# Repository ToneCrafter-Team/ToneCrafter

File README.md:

<h1 align=left>&emsp;ToneCrafter</h1>

ToneCrafter is a project developped by students at [ENSEA](https://www.ensea.fr/).  
Our goal is to develop an algorithm capable of analyzing any audio file containing guitar sounds and retrieve its parameters. ToneCrafter will then generate a numeric filter that will modulate your guitar sound and make it sound like the recording you fed it. Exciting isn't it ?  
We are also working on a hardware implementation using a STM32 µC that will allow musicians to use ToneCrafter on stage and tune the different parameters.

- [Our work so far](#our-work-so-far)
  * [Software](#Software)
  * [Hardware](#Hardware)
- [How to use ToneCrafter](#how-to-use-tonecrafter)
  * [Installing Anaconda and TensorFlow](#installing-anaconda-and-tensorflow)
  * [Dataset](#dataset)
  * [Useful links](#useful-links)
- [What's next ?](#whats-next-)

## Our work so far
### Software
We started out trying to use Magenta's [DDSP](https://www.github.com/magenta/ddsp), but this was a bit too ambitious for AI newbies like us, so we tried implementing our own algorithms.  
This sparked three different approaches to our problem:  
  * A CNN based approach where we tried to teach a neural network to recreate a distortion.
  * A "bare coding" approach using math and clever algorithms to recreate a distortion from an audio file
  * A VAE based approach trying to recreate the mechanisms behind Magenta's DDSP

### Hardware
We started working on different PCB designs using [Eagle](https://www.autodesk.com/products/eagle/overview) and working on a STM32F7 discovery kit for testing purposes.

## How to use ToneCrafter
### Installing Anaconda and TensorFlow
To begin with, if you want to work locally and not on Colabs as we did, you will have to install Anaconda.
To do this follow the [officials instructions](https://docs.anaconda.com/anaconda/user-guide/tasks/tensorflow/) that are given to you.  

If you want to try the huge potential of DDSP, let’s check the [DDSP GitHub](https://github.com/magenta/ddsp) which show how to install it.
There are also some tutorials to introduce the main concepts of the library (that we strongly recommend you to do) and demos to show what you can do with it (Like Timbre transfer, Train Autoencoder and Pitch Detection).

And then, if you want to have fun on the models created by the Google team with the [Magenta](https://magenta.tensorflow.org/) project, follow the installation guide on their [page](https://github.com/magenta/magenta).

### Dataset
To train our CNN, we searched for a dataset containing clean audio from a guitar and different distortions. As we could not find any we had to create our own. We recorded a guitar for 1 minute and added various levels of distortion. To increase the size of our base, we applied an EQ filter with various settings.  
We ended up with a lot of .wav files that you can find [here](https://github.com/ToneCrafter-Team/ToneCrafter/tree/main/Software/CNN%20Models/Dataset).  
In order to train our CNN, we splitted our files in 200ms chunks using our [Preparing Data Notebook](https://github.com/ToneCrafter-Team/ToneCrafter/blob/main/Software/CNN%20Models/Preparing_Data.ipynb)  
We then organised our files in the following way :  

- X_train :  
  * Clean  
  * Clean_TrebbleBoost  
  * Clean_BassBoost  
  * Clean_BassCut  

- y_train :
  * Disto  
  * Disto_TrebbleBoost  
  * Disto_BassBoost  
  * Disto_BassCut  

- Validation data :
  * Clean_TrebbleCut as X_valid  
  * Disto_TrebbleCut as y_valid  

We are concious that this dataset is far from perfect (please don't listen to it, the guitar playing is awful) from a recording standpoint and the way we splitted our audio might cause some problems.

For the maths oriented approach, we used the excellent [IDMT-SMT-Audio_Effects Dataset](https://www.idmt.fraunhofer.de/en/business_units/m2d/smt/audio_effects.html), which enabled us to link each note played to it's distorted counterpart.  

<span style="color:red"> *For a more in-depths version of this readme, checkout our (magnificent) project report available in both French and English at the root of this repository*</span>
## What's next ?
As of the 03/05/2021, our yearly project has ended. We will continue to work on ToneCrafter at a lighter pace, as we'll be completing our summer internships. If all goes well, some new students will pick up the project in the fall to continue to build on top of our work. In the mean time, don't hesitate to take part in our project, via issues or pull requests.

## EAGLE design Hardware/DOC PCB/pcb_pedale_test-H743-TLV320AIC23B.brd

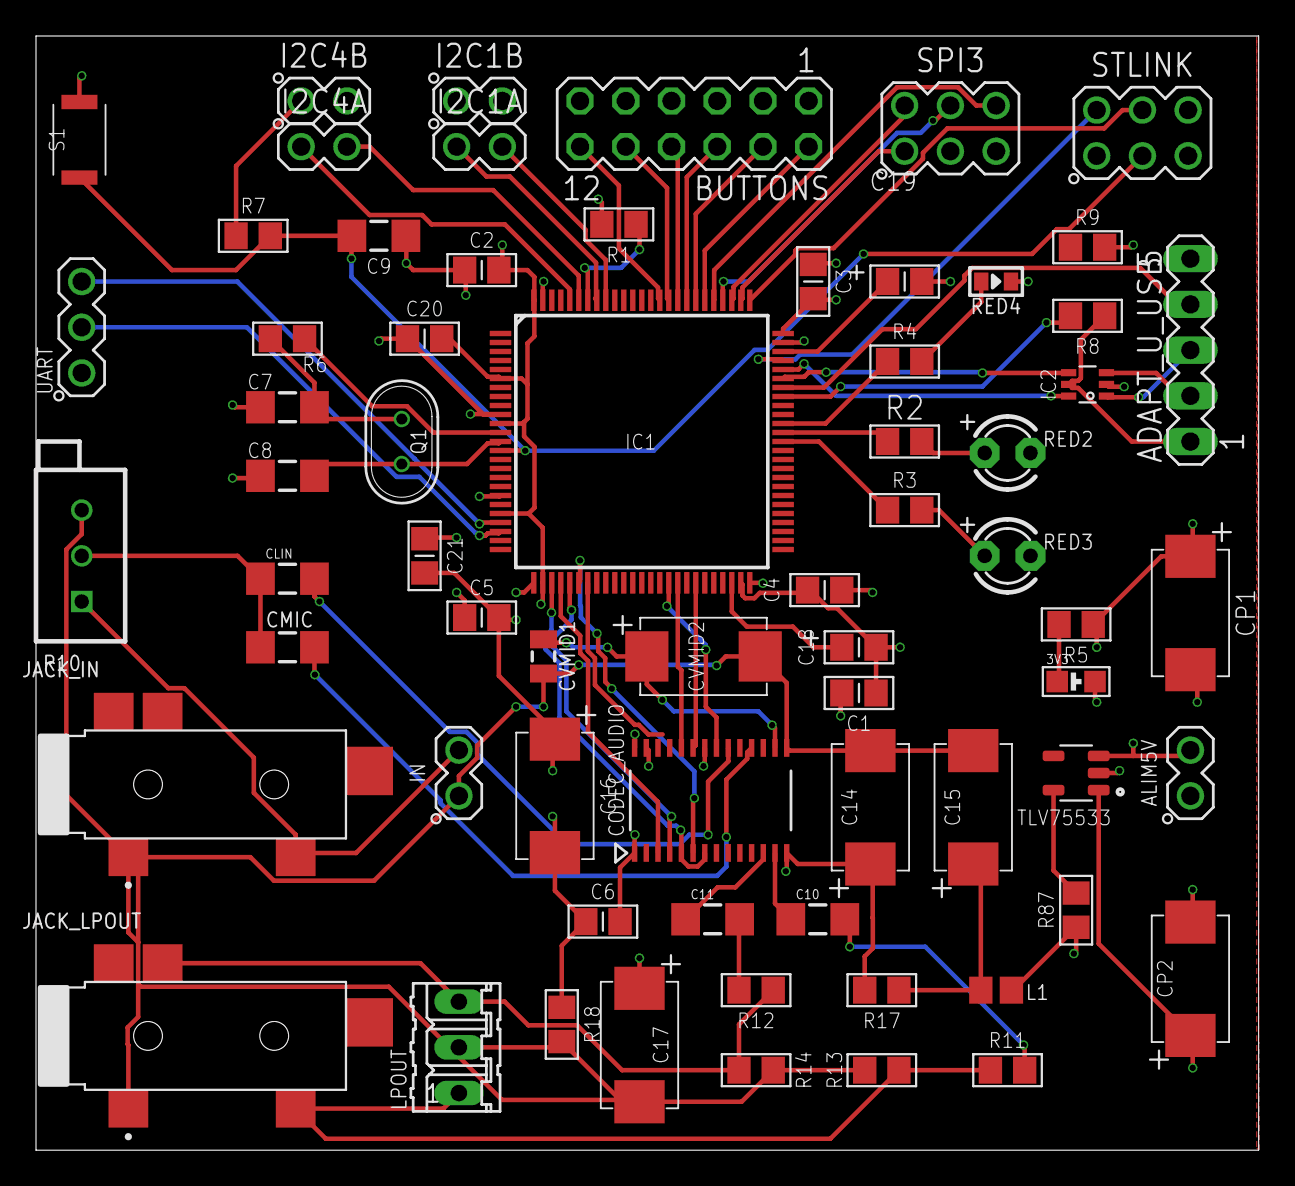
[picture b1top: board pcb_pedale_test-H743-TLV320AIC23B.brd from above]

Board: 4 copper layers, 67.9 x 61.9 mm, 67 parts (0 on the bottom side), 65 nets.

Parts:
3V3: 0805-LED
ADAPT_U_USB: MA05-1
ALIM5V: MA02-1
BUTTONS: MA06-2
C1, C2, C3, C4, C5, C20, C21: 0.1uF; C0805
C6: 0.1u; C0805
C7, C8: 12pF; 1206
C9: 0.1uF; 1206
C10, C11: 1u; 1206
C14, C15, C16, C17: 10u; CPOL2917
C18, C19: 2.2u; CPOL0805
CLIN: 1u; 1206
CMIC: 1u; 1206
CODEC_AUDIO: TLV320AIC23B; TSSOP28
CP1: 100 uF; CPOL2917
CP2: 10u; CPOL2917
CVMID1: 100n; 0805-CAP
CVMID2: 10u; CPOL2917
I2C1A, I2C1B, I2C4A, I2C4B: MA02-1
IC1: STM32H743VIT1Q; LQFP100_14X14
IC2: SC70-6
IN: MA02-1
JACK_IN: 35RASMT4BHNTRX
JACK_LPOUT: 35RASMT4BHNTRX
L1: FB805
LPOUT: 03P
Q1: 16MHz; Q-HC-46X
R1: 10K; R0805
R2, R3, R4: 180; R0805
R5: 1k; R0805
R6, R11, R12: 100; R0805
R7, R13, R14: 100k; R0805
R8: 4.7k; R0805
R9: 10k; R0805
R10: POT-PTH
R17: 2.2; R0805
R18, R87: 0; R0805
RED2, RED3: LED3MM
RED4: 0603-LED
S1: SWITCH-SKRKAEE020; SKRKAEE020
SPI3: MA03-2
STLINK: 75867-331LF; MA03-2
TLV75533: TLV75533PDBVR; SOT95P280X145-5N
UART: MA03-1

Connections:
3V3: C1.2, C2.2, C3.2, C4.2, C5.2, C6.2, C16.+, C20.2, C21.2, CODEC_AUDIO.1, CODEC_AUDIO.22, CODEC_AUDIO.27, CP1.+, I2C1B.2, I2C4B.1, IC1.6, IC1.11, IC1.21, IC1.27, IC1.50, IC1.75, IC1.100, L1.1, R5.1, R7.1, R87.1, SPI3.5, STLINK.1
3V3A: C14.+, C17.+, CODEC_AUDIO.14, R17.2
5V: ALIM5V.2, CP2.+, TLV75533.1, TLV75533.3
AGND: C14.-, C15.-, C17.-, CODEC_AUDIO.15, CVMID1.2, CVMID2.-, IN.1, JACK_IN.1, JACK_LPOUT.1, LPOUT.2, R10.3, R13.2, R14.2, R18.2
DM: ADAPT_U_USB.2, IC2.3
DP: ADAPT_U_USB.3, IC2.1
GND: 3V3.C, ADAPT_U_USB.5, ALIM5V.1, BUTTONS.1, BUTTONS.3, BUTTONS.5, BUTTONS.7, BUTTONS.9, BUTTONS.11, C1.1, C2.1, C3.1, C4.1, C5.1, C6.1, C7.1, C8.1, C9.1, C16.-, C18.2-, C19.2-, C20.1, C21.1, CODEC_AUDIO.28, CP1.-, CP2.-, I2C1B.1, I2C4B.2, IC1.10, IC1.19, IC1.26, IC1.49, IC1.74, IC1.99, IC2.2, R1.2, R9.2, R18.1, RED2.K, RED3.K, RED4.C, S1.1, SPI3.3, STLINK.5, TLV75533.2, UART.1
HOME: BUTTONS.12, IC1.86
I2S_CK: CODEC_AUDIO.3, IC1.29
I2S_DI: CODEC_AUDIO.4, IC1.30
I2S_DO: CODEC_AUDIO.6, IC1.31
I2S_MCK: CODEC_AUDIO.25, IC1.32
I2S_WS: CODEC_AUDIO.5, CODEC_AUDIO.7, IC1.28
JACK_OUT_L: JACK_LPOUT.2, LPOUT.3, R12.1, R14.1
JACK_OUT_R: JACK_LPOUT.3, LPOUT.1, R11.1, R13.1
LED2_PWM: IC1.64, R2.1
LED3_PWM: IC1.63, R3.1
LED4_PWM: IC1.65, R4.1
LOUT: C11.1, CODEC_AUDIO.12
MICIN: CMIC.2, CODEC_AUDIO.18
unnamed: IC1.94, R1.1
unnamed: C11.2, R12.2
unnamed: R2.2, RED2.A
unnamed: IC1.12, R6.1
unnamed: R3.2, RED3.A
unnamed: C10.2, R11.2
unnamed: CLIN.2, CODEC_AUDIO.20
unnamed: C15.+, L1.2, R17.1
unnamed: C18.1+, IC1.48
unnamed: C19.1+, IC1.73
unnamed: CLIN.1, CMIC.1, R10.2
unnamed: IN.2, JACK_IN.3, R10.1
unnamed: R4.2, RED4.A
unnamed: CODEC_AUDIO.16, CVMID1.1, CVMID2.+
unnamed: 3V3.A, R5.2
unnamed: C7.2, Q1.1, R6.2
unnamed: R87.2, TLV75533.5
NRST: C9.2, IC1.14, R7.2, S1.2, STLINK.3
OSC_OUT: C8.2, IC1.13, Q1.2
PRESSION: BUTTONS.6, IC1.83
ROTATE_X: BUTTONS.4, IC1.82
ROTATE_Y: BUTTONS.2, IC1.81
ROUT: C10.1, CODEC_AUDIO.13
RX: IC1.23, UART.2
SCL_1: I2C4A.2, IC1.95
SCL_4: I2C1A.2, IC1.92
SDA_1: I2C4A.1, IC1.96
SDA_4: I2C1A.1, IC1.93
SPI3_MISO: IC1.79, SPI3.4
SPI3_MOSI: IC1.80, SPI3.6
SPI3_NSS: IC1.77, SPI3.1
SPI3_SCK: IC1.78, SPI3.2
SPI4_MOSI: CODEC_AUDIO.23, IC1.44
SPI4_NSS: CODEC_AUDIO.21, IC1.41
SPI4_SCK: CODEC_AUDIO.24, IC1.42
STOMP1: BUTTONS.8, IC1.84
STOMP2: BUTTONS.10, IC1.85
SWCLK: IC1.76, STLINK.4
SWDIO: IC1.72, STLINK.2
TX: IC1.22, UART.3
USB_ID: ADAPT_U_USB.4, IC1.69
USB_OTG_FS_DM: IC1.70, IC2.4
USB_OTG_FS_DP: IC1.71, IC2.6
USB_OTG_FS_VBUS: ADAPT_U_USB.1, IC2.5, R8.1
USB_OTG_FS_VBUS_3V3: IC1.68, R8.2, R9.1

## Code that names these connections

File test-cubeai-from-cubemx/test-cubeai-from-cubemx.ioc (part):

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Mcu.Name=STM32F746NGHx
Mcu.Package=TFBGA216
Mcu.UserName=STM32F746NGHx
PA0/WKUP.GPIOParameters=GPIO_PuPd,GPIO_Label,GPIO_Mode
PA0/WKUP.GPIO_Label=ARDUINO A0
PA0/WKUP.GPIO_Mode=GPIO_MODE_ANALOG
PA0/WKUP.GPIO_PuPd=GPIO_NOPULL
PA0/WKUP.Signal=ADCx_IN0
PA1.GPIOParameters=GPIO_Label
PA1.GPIO_Label=RMII_REF_CLK [LAN8742A-CZ-TR_REFCLK0]
PA1.Mode=RMII
PA1.Signal=ETH_REF_CLK
PA10.GPIOParameters=GPIO_Label
PA10.GPIO_Label=OTG_FS_ID
PA10.Signal=USB_OTG_FS_ID
PA11.GPIOParameters=GPIO_Label
PA11.GPIO_Label=OTG_FS_N
PA11.Mode=Host_Only
PA11.Signal=USB_OTG_FS_DM
PA12.GPIOParameters=GPIO_Label
PA12.GPIO_Label=OTG_FS_P
PA12.Mode=Host_Only
PA12.Signal=USB_OTG_FS_DP
PA13.GPIOParameters=GPIO_Label
PA13.GPIO_Label=SWDIO
PA13.Mode=Serial_Wire
PA13.Signal=SYS_JTMS-SWDIO
PA14.GPIOParameters=GPIO_Label
PA14.GPIO_Label=SWCLK
PA14.Mode=Serial_Wire
PA14.Signal=SYS_JTCK-SWCLK
PA15.GPIOParameters=GPIO_ModeDefaultPP,GPIO_Speed,GPIO_PuPd,GPIO_Label
PA15.GPIO_Label=ARDUINO PWM/D9
PA15.GPIO_ModeDefaultPP=GPIO_MODE_AF_PP
PA15.GPIO_PuPd=GPIO_NOPULL
PA15.GPIO_Speed=GPIO_SPEED_FREQ_LOW
PA15.Signal=S_TIM2_CH1_ETR
PA2.GPIOParameters=GPIO_Label
PA2.GPIO_Label=RMII_MDIO [LAN8742A-CZ-TR_MDIO]
PA2.Mode=RMII
PA2.Signal=ETH_MDIO
PA3.GPIOParameters=GPIO_Label
PA3.GPIO_Label=ULPI_D0 [USB3320C-EZK_D0]
PA3.Mode=Host_HS
PA3.Signal=USB_OTG_HS_ULPI_D0
PA4.GPIOParameters=GPIO_Label
PA4.GPIO_Label=DCMI_HSYNC
PA4.Mode=Slave_8_bits_External_Synchro
PA4.Signal=DCMI_HSYNC
PA5.GPIOParameters=GPIO_Label
PA5.GPIO_Label=ULPI_CLK [USB3320C-EZK_CLKOUT]
PA5.Mode=Host_HS
PA5.Signal=USB_OTG_HS_ULPI_CK
PA6.Mode=Slave_8_bits_External_Synchro
PA6.Signal=DCMI_PIXCLK
PA7.GPIOParameters=GPIO_Label
PA7.GPIO_Label=RMII_CRS_DV [LAN8742A-CZ-TR_CRS_DV]
PA7.Mode=RMII
PA7.Signal=ETH_CRS_DV
PA8.GPIOParameters=GPIO_ModeDefaultPP,GPIO_Speed,GPIO_PuPd,GPIO_Label
PA8.GPIO_Label=ARDUINO PWM/D10
PA8.GPIO_ModeDefaultPP=GPIO_MODE_AF_PP
PA8.GPIO_PuPd=GPIO_NOPULL
PA8.GPIO_Speed=GPIO_SPEED_FREQ_LOW
PA8.Signal=S_TIM1_CH1
PA9.GPIOParameters=GPIO_Speed,GPIO_PuPd,GPIO_Label,GPIO_Mode
PA9.GPIO_Label=VCP_TX [STM32F103CBT6_PA3]
PA9.GPIO_Mode=GPIO_MODE_AF_PP
PA9.GPIO_PuPd=GPIO_NOPULL
PA9.GPIO_Speed=GPIO_SPEED_FREQ_LOW
PA9.Mode=Asynchronous
PA9.Signal=USART1_TX
PB0.GPIOParameters=GPIO_Label
PB0.GPIO_Label=ULPI_D1 [USB3320C-EZK_D1]
PB0.Mode=Host_HS
PB0.Signal=USB_OTG_HS_ULPI_D1
PB1.GPIOParameters=GPIO_Label
PB1.GPIO_Label=ULPI_D2 [USB3320C-EZK_D2]
PB1.Mode=Host_HS
PB1.Signal=USB_OTG_HS_ULPI_D2
PB10.GPIOParameters=GPIO_Label
PB10.GPIO_Label=ULPI_D3 [USB3320C-EZK_D3]
PB10.Signal=USB_OTG_HS_ULPI_D3
PB11.GPIOParameters=GPIO_Label
PB11.GPIO_Label=ULPI_D4 [USB3320C-EZK_D4]
PB11.Mode=Host_HS
PB11.Signal=USB_OTG_HS_ULPI_D4
PB12.GPIOParameters=GPIO_Label
PB12.GPIO_Label=ULPI_D5 [USB3320C-EZK_D5]
PB12.Mode=Host_HS
PB12.Signal=USB_OTG_HS_ULPI_D5
PB13.GPIOParameters=GPIO_Label
PB13.GPIO_Label=ULPI_D6 [USB3320C-EZK_D6]
PB13.Mode=Host_HS
PB13.Signal=USB_OTG_HS_ULPI_D6
PB14.GPIOParameters=GPIO_Speed,GPIO_PuPd,GPIO_Label,GPIO_Mode
PB14.GPIO_Label=ARDUINO MISO/D12
PB14.GPIO_Mode=GPIO_MODE_AF_PP
PB14.GPIO_PuPd=GPIO_NOPULL
PB14.GPIO_Speed=GPIO_SPEED_FREQ_LOW
PB14.Signal=SPI2_MISO
PB15.GPIOParameters=GPIO_Speed,GPIO_PuPd,GPIO_Label,GPIO_Mode
PB15.GPIO_Label=ARDUINO MOSI/PWM/D11
PB15.GPIO_Mode=GPIO_MODE_AF_PP
PB15.GPIO_PuPd=GPIO_NOPULL
PB15.GPIO_Speed=GPIO_SPEED_FREQ_LOW
PB15.Signal=SPI2_MOSI
PB2.Mode=Single Bank 1
PB2.Signal=QUADSPI_CLK
PB3.GPIOParameters=GPIO_Label
PB3.GPIO_Label=SWO
PB3.Signal=SYS_JTDO-SWO
PB4.GPIOParameters=GPIO_ModeDefaultPP,GPIO_Speed,GPIO_PuPd,GPIO_Label
PB4.GPIO_Label=ARDUINO PWM/D3
PB4.GPIO_ModeDefaultPP=GPIO_MODE_AF_PP
PB4.GPIO_PuPd=GPIO_NOPULL
PB4.GPIO_Speed=GPIO_SPEED_FREQ_LOW
PB4.Signal=S_TIM3_CH1
PB5.GPIOParameters=GPIO_Label
PB5.GPIO_Label=ULPI_D7 [USB3320C-EZK_D7]
PB5.Mode=Host_HS
PB5.Signal=USB_OTG_HS_ULPI_D7
PB6.GPIOParameters=GPIO_Label
PB6.GPIO_Label=QSPI_NCS [N25Q128A13EF840E_S]
PB6.Mode=Single Bank 1
PB6.Signal=QUADSPI_BK1_NCS
PB7.GPIOParameters=GPIO_Speed,GPIO_PuPd,GPIO_Label,GPIO_Mode
PB7.GPIO_Label=VCP_RX [STM32F103CBT6_PA2]
PB7.GPIO_Mode=GPIO_MODE_AF_PP
PB7.GPIO_PuPd=GPIO_NOPULL
PB7.GPIO_Speed=GPIO_SPEED_FREQ_LOW
PB7.Mode=Asynchronous
PB7.Signal=USART1_RX
PB8.GPIOParameters=GPIO_Speed,GPIO_PuPd,GPIO_Label,GPIO_Pu,GPIO_Mode
PB8.GPIO_Label=ARDUINO SCL/D15
PB8.GPIO_Mode=GPIO_MODE_AF_OD
PB8.GPIO_Pu=GPIO_PULLUP
PB8.GPIO_PuPd=GPIO_NOPULL
PB8.GPIO_Speed=GPIO_SPEED_FREQ_LOW
PB8.Mode=I2C
PB8.Signal=I2C1_SCL
PB9.GPIOParameters=GPIO_Speed,GPIO_PuPd,GPIO_Label,GPIO_Pu,GPIO_Mode
PB9.GPIO_Label=ARDUINO SDA/D14
PB9.GPIO_Mode=GPIO_MODE_AF_OD
PB9.GPIO_Pu=GPIO_PULLUP
PB9.GPIO_PuPd=GPIO_NOPULL
PB9.GPIO_Speed=GPIO_SPEED_FREQ_LOW
PB9.Mode=I2C
PB9.Signal=I2C1_SDA
PC0.GPIOParameters=GPIO_Label
PC0.GPIO_Label=ULPI_STP [USB3320C-EZK_STP]
PC0.Mode=Host_HS
PC0.Signal=USB_OTG_HS_ULPI_STP
PC1.GPIOParameters=GPIO_Label
PC1.GPIO_Label=RMII_MDC [LAN8742A-CZ-TR_MDC]
PC1.Mode=RMII
PC1.Signal=ETH_MDC
PC10.GPIOParameters=GPIO_Label
PC10.GPIO_Label=SDMMC_D2
PC10.Mode=SD_4_bits_Wide_bus
PC10.Signal=SDMMC1_D2
PC11.GPIOParameters=GPIO_Label
PC11.GPIO_Label=SDMMC_D3
PC11.Mode=SD_4_bits_Wide_bus
PC11.Signal=SDMMC1_D3
PC12.GPIOParameters=GPIO_Label
PC12.GPIO_Label=SDMMC_CK
PC12.Mode=SD_4_bits_Wide_bus
PC12.Signal=SDMMC1_CK
PC13.GPIOParameters=GPIO_Label
PC13.GPIO_Label=uSD_Detect
PC13.Signal=GPIO_Input
PC14/OSC32_IN.GPIOParameters=GPIO_Label
PC14/OSC32_IN.GPIO_Label=RCC_OSC32_IN
PC14/OSC32_IN.Mode=LSE-External-Oscillator
PC14/OSC32_IN.Signal=RCC_OSC32_IN
PC15/OSC32_OUT.GPIOParameters=GPIO_Label
PC15/OSC32_OUT.GPIO_Label=RCC_OSC32_OUT
PC15/OSC32_OUT.Mode=LSE-External-Oscillator
PC15/OSC32_OUT.Signal=RCC_OSC32_OUT
PC2.GPIOParameters=GPIO_Label
PC2.GPIO_Label=ULPI_DIR [USB3320C-EZK_DIR]
PC2.Mode=Host_HS
PC2.Signal=USB_OTG_HS_ULPI_DIR
PC3.GPIOParameters=GPIO_Label
PC3.GPIO_Label=FMC_SDCKE0 [MT48LC4M32B2B5-6A_CKE]
PC3.Mode=SdramChipSelect1_1
PC3.Signal=FMC_SDCKE0
PC4.GPIOParameters=GPIO_Label
PC4.GPIO_Label=RMII_RXD0 [LAN8742A-CZ-TR_RXD0]
PC4.Mode=RMII
PC4.Signal=ETH_RXD0
PC5.GPIOParameters=GPIO_Label
PC5.GPIO_Label=RMII_RXD1 [LAN8742A-CZ-TR_RXD1]
PC5.Mode=RMII
PC5.Signal=ETH_RXD1
PC6.GPIOParameters=GPIO_Label
PC6.GPIO_Label=ARDUINO TX/D1
PC6.Mode=Asynchronous
PC6.Signal=USART6_TX
PC7.GPIOParameters=GPIO_Label
PC7.GPIO_Label=ARDUINO RX/D0
PC7.Mode=Asynchronous
PC7.Signal=USART6_RX
PC8.Mode=SD_4_bits_Wide_bus
PC8.Signal=SDMMC1_D0
PC9.Mode=SD_4_bits_Wide_bus
PC9.Signal=SDMMC1_D1
PD0.GPIOParameters=GPIO_Label
PD0.GPIO_Label=FMC_D2 [MT48LC4M32B2B5-6A_DQ2]
PD0.Signal=FMC_D2_DA2
PD1.GPIOParameters=GPIO_Label
PD1.GPIO_Label=FMC_D3 [MT48LC4M32B2B5-6A_DQ3]
PD1.Signal=FMC_D3_DA3
PD10.GPIOParameters=GPIO_Label
PD10.GPIO_Label=FMC_D15 [MT48LC4M32B2B5-6A_DQ15]
PD10.Signal=FMC_D15_DA15
PD11.GPIOParameters=GPIO_Label
PD11.GPIO_Label=QSPI_D0 [N25Q128A13EF840E_DQ0]
PD11.Mode=Single Bank 1
PD11.Signal=QUADSPI_BK1_IO0
PD12.GPIOParameters=GPIO_Label
PD12.GPIO_Label=QSPI_D1 [N25Q128A13EF840E_DQ1]
PD12.Mode=Single Bank 1
PD12.Signal=QUADSPI_BK1_IO1
PD13.GPIOParameters=GPIO_Label
PD13.GPIO_Label=QSPI_D3 [N25Q128A13EF840E_DQ3]
PD13.Mode=Single Bank 1
PD13.Signal=QUADSPI_BK1_IO3
PD14.GPIOParameters=GPIO_Label
PD14.GPIO_Label=FMC_D0 [MT48LC4M32B2B5-6A_DQ0]
PD14.Signal=FMC_D0_DA0
PD15.GPIOParameters=GPIO_Label
PD15.GPIO_Label=FMC_D1 [MT48LC4M32B2B5-6A_DQ1]
PD15.Signal=FMC_D1_DA1
PD2.GPIOParameters=GPIO_Label
PD2.GPIO_Label=SDMMC_CMD
PD2.Mode=SD_4_bits_Wide_bus
PD2.Signal=SDMMC1_CMD
PD3.GPIOParameters=GPIO_Label
PD3.GPIO_Label=DCMI_D5
PD3.Mode=Slave_8_bits_External_Synchro
PD3.Signal=DCMI_D5
PD4.GPIOParameters=GPIO_Label
PD4.GPIO_Label=OTG_FS_OverCurrent [STMPS2141STR_Fault]
PD4.Signal=GPIO_Input
PD5.GPIOParameters=PinState,GPIO_Label
PD5.GPIO_Label=OTG_FS_PowerSwitchOn [STMPS2141STR_EN]
PD5.PinState=GPIO_PIN_SET
PD5.Signal=GPIO_Output
PD6.GPIOParameters=GPIO_Label,GPIO_ModeDefaultEXTI
PD6.GPIO_Label=Audio_INT
PD6.GPIO_ModeDefaultEXTI=GPIO_MODE_EVT_RISING
PD6.Signal=GPXTI6
PD7.GPIOParameters=GPIO_Label
PD7.GPIO_Label=SPDIF_RX0 [74LVC1G04SE_4]
PD7.Mode=IN0
PD7.Signal=SPDIFRX_IN0
PD8.GPIOParameters=GPIO_Label
PD8.GPIO_Label=FMC_D13 [MT48LC4M32B2B5-6A_DQ13]
PD8.Signal=FMC_D13_DA13
PD9.GPIOParameters=GPIO_Label
PD9.GPIO_Label=FMC_D14 [MT48LC4M32B2B5-6A_DQ14]
PD9.Signal=FMC_D14_DA14
PE0.GPIOParameters=GPIO_Label
PE0.GPIO_Label=FMC_NBL0 [MT48LC4M32B2B5-6A_DQM0]
PE0.Signal=FMC_NBL0
PE1.GPIOParameters=GPIO_Label
PE1.GPIO_Label=FMC_NBL1 [MT48LC4M32B2B5-6A_DQM1]
PE1.Signal=FMC_NBL1
PE10.GPIOParameters=GPIO_Label
PE10.GPIO_Label=FMC_D7 [MT48LC4M32B2B5-6A_DQ7]
PE10.Signal=FMC_D7_DA7
PE11.GPIOParameters=GPIO_Label
PE11.GPIO_Label=FMC_D8 [MT48LC4M32B2B5-6A_DQ8]
PE11.Signal=FMC_D8_DA8
PE12.GPIOParameters=GPIO_Label
PE12.GPIO_Label=FMC_D9 [MT48LC4M32B2B5-6A_DQ9]
PE12.Signal=FMC_D9_DA9
PE13.GPIOParameters=GPIO_Label
PE13.GPIO_Label=FMC_D10 [MT48LC4M32B2B5-6A_DQ10]
PE13.Signal=FMC_D10_DA10
PE14.GPIOParameters=GPIO_Label
PE14.GPIO_Label=FMC_D11 [MT48LC4M32B2B5-6A_DQ11]
PE14.Signal=FMC_D11_DA11
PE15.GPIOParameters=GPIO_Label
PE15.GPIO_Label=FMC_D12 [MT48LC4M32B2B5-6A_DQ12]
PE15.Signal=FMC_D12_DA12

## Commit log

2021-01-25 Add files via upload
    added project's logo
2021-01-25 Update README.md
    Added logo & more information about our project's structure
2021-01-25 Update README.md
    resized logo, fixed titles
2021-03-12 Dataset generation
    This IPython Notebook was used to create our dataset from 30 wav files of a guitar recording with various distortion parameters.
    This resulted in 8670 200ms audio files that we'll use to train our CNN.
2021-03-16 Add files via upload
    Notebook to try to use an optimized style transfer for our purpose.
2021-03-23 Added Files
    First try at a Keras model for our project, used to experiment with different layers & activation functions.
2021-04-07 Rename Distortion_test.py to Effect creation & research/Distortion_test.py
    moved to Effect creation & research folder.
2021-04-07 Rename Test_des_Effets_DDSP_et_Magenta.ipynb to Effect creation & research/Test_des_Effets_DDSP_et_Magenta.ipynb
    moved to Effect creation & research folder
2021-04-07 Rename Ecoute_Temps_reel_Test.py to Effect creation & research/Ecoute_Temps_reel_Test.py
    moved to Effect creation & research folder
2021-04-07 Rename Model_test.ipynb to CNN Models/Model_test.ipynb
    moved to Effect creation & research folder
2021-04-07 Rename Preparing_Data.ipynb to CNN Models/Preparing_Data.ipynb
    moved to CNN Models folder
2021-04-07 Update README.md
    Added quick update concerning our new approach using CNN
2021-04-07 Add files via upload
    Updated version of our 1st model, we're using the MFCC (Mel Frequency Cepstral Coefficients) of our audio instead of an STFT (Short Time Fourier Transform).
    We're now processing our audio in the same IPython Notebook as our model, as we've had problem formatting our data into a CSV, we will look into that problem in the future.
2021-04-07 Add files via upload
    Optimized data processing
    Added validation data
    Added Early Stopping
2021-04-08 Add files via upload
    ##Data processing :
    Changed MFCC resolution (n_mfcc=40->128)
    Fixed sample rate in librosa.mfcc call (22050->44100)
    ##Model :
    Added BatchNormalization layer
    Added Dense Layer
2021-04-19 Create Doc PCB
2021-05-01 Rename instructionsVAEV4.txt to instructionsVAEVX.txt
2021-05-01 Rename instructionsVAEVX.txt to instructions_vaeVx.txt
2021-05-04 File arrangement
2021-05-04 Add files via upload
    Changed NN disposition with a succession of Conv1D & MaxPool1D
    Added a spectrogram of the whole data rather than a spectrogram for a single sample
2021-05-04 Add Dataset
2021-05-04 Add Dataset
    Add the rest of the database
2021-05-04 This a test to push from Atom
2021-05-04 Test
2021-05-04 Read me update
2021-05-04 added Dataset section fixed formatting issues
2021-05-04 fixed toc issues
2021-05-04 Updated "What's next" section
2021-05-04 hopefully fixed all the inconsistencies in our TOC
2021-05-04 update the installation part
2021-05-04 Update CNN Models MFCC
2021-05-08 Final project report
    Final report on our project, be sure to open it on Adobe Acrobat or equivalent to be able to listen to the embedded audio files
2021-05-08 Add files via upload
    English version of our project report
    -Corrected a few typos
    -Formatting
2021-05-08 Update README.md
    added reference to our report
    removed empty section
2021-05-11 Create wololo
2021-05-11 Rename Software/Approche Paramétrique/overdrive.py to Software/Parametric Approach
2021-05-11 Create adrien
2021-05-11 Update and rename adrien to Databases Link
2021-05-11 Add files via upload
    Toute la partie d'Adrien
2021-12-13 Test CubeAI
